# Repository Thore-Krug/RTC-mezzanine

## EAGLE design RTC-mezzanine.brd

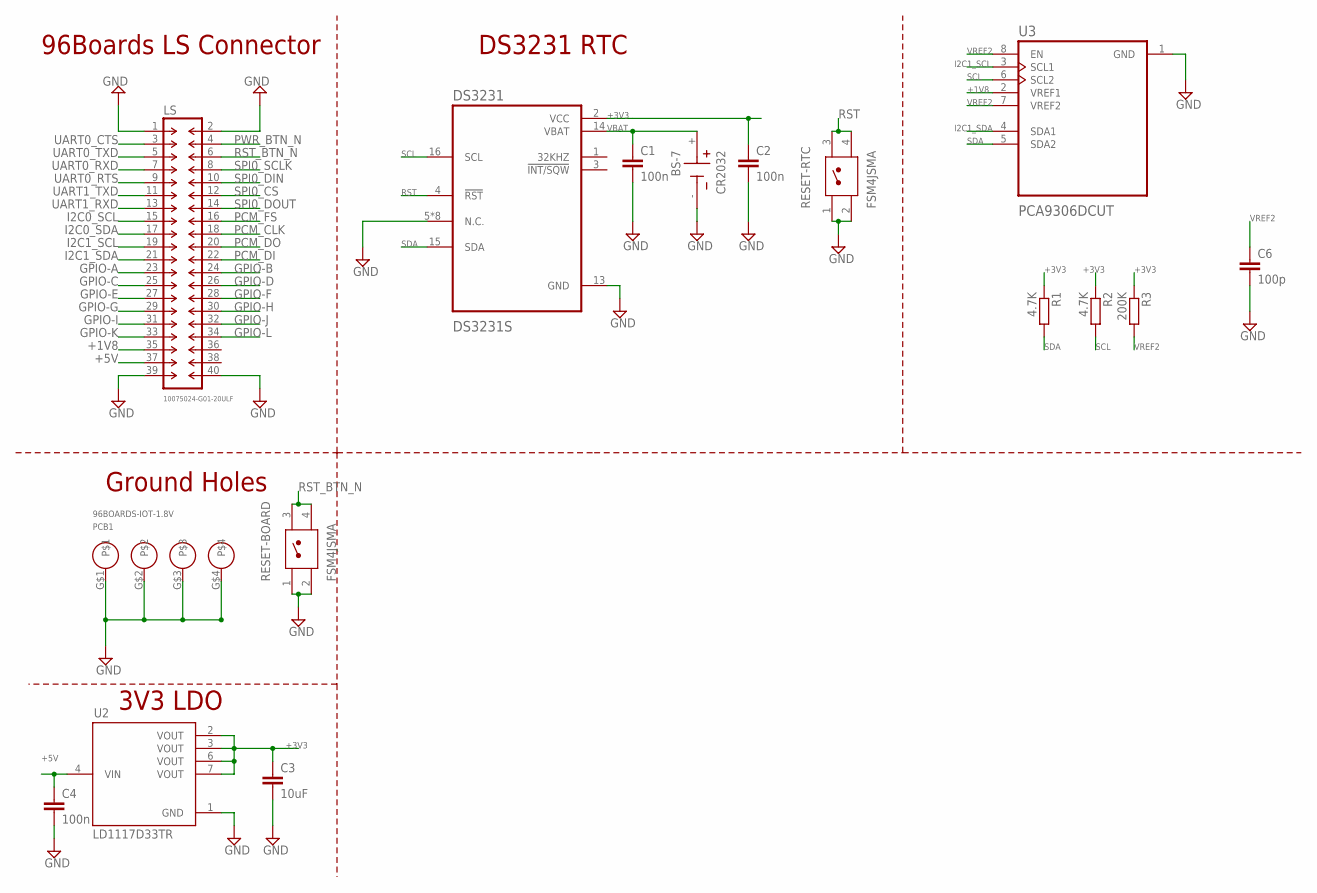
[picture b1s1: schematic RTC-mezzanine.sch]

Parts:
C1, C2, C4: 100n; C0603
C3: 10uF; C0805
C6: 100p; C0603
CR2032: BS-7; BAT_BS-7
DS3231: DS3231S; SOIC127P1032X265-16N
LS: 10075024-G01-20ULF
PCB1: 96BOARDS-IOT-1.8V
R1, R2: 4.7K; R0603
R3: 200K; R0603
RESET-BOARD: FSM4JSMA; TE_FSM4JSMA
RESET-RTC: FSM4JSMA; TE_FSM4JSMA
U2: LD1117D33TR; SOIC127P600X175-8N
U3: PCA9306DCUT; SOP50P310X90-8N

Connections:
+1V8: LS.35, U3.2 (VREF1)
+3V3: C2.1, C3.1, DS3231.2 (VCC), R1.1, R2.1, R3.1, U2.2 (VOUT), U2.3 (VOUT), U2.6 (VOUT), U2.7 (VOUT)
+5V: C4.1, LS.37, U2.4 (VIN)
GND: C1.2, C2.2, C3.2, C4.2, C6.2, CR2032.-, DS3231.5 (N.C.), DS3231.6 (N.C.), DS3231.7 (N.C.), DS3231.8 (N.C.), DS3231.9 (N.C.), DS3231.10 (N.C.), DS3231.11 (N.C.), DS3231.12 (N.C.), DS3231.13 (GND), LS.2, LS.39, LS.40, PCB1.G$1, PCB1.G$2, PCB1.G$3, PCB1.G$4, RESET-BOARD.1, RESET-BOARD.2, RESET-RTC.1, RESET-RTC.2, U2.1 (GND), U3.1 (GND)
GPIO-A: LS.23
GPIO-B: LS.24
GPIO-C: LS.25
GPIO-D: LS.26
GPIO-E: LS.27
GPIO-F: LS.28
GPIO-G: LS.29
GPIO-H: LS.30
GPIO-I: LS.31
GPIO-J: LS.32
GPIO-K: LS.33
GPIO-L: LS.34
I2C0_SCL: LS.15
I2C0_SDA: LS.17
I2C1_SCL: LS.19, U3.3 (SCL1)
I2C1_SDA: LS.21, U3.4 (SDA1)
PCM_CLK: LS.18
PCM_DI: LS.22
PCM_DO: LS.20
PCM_FS: LS.16
PWR_BTN_N: LS.4
RST: DS3231.4 (!RST), RESET-RTC.3, RESET-RTC.4
RST_BTN_N: LS.6, RESET-BOARD.3, RESET-BOARD.4
SCL: DS3231.16 (SCL), R2.2, U3.6 (SCL2)
SDA: DS3231.15 (SDA), R1.2, U3.5 (SDA2)
SPI0_CS: LS.12
SPI0_DIN: LS.10
SPI0_DOUT: LS.14
SPI0_SCLK: LS.8
UART0_CTS: LS.3
UART0_RTS: LS.9
UART0_RXD: LS.7
UART0_TXD: LS.5
UART1_RXD: LS.13
UART1_TXD: LS.11
VBAT: C1.1, CR2032.+, DS3231.14 (VBAT)
VREF2: C6.1, R3.2, U3.7 (VREF2), U3.8 (EN)

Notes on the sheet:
96Boards LS Connector
Ground Holes
DS3231 RTC
3V3 LDO

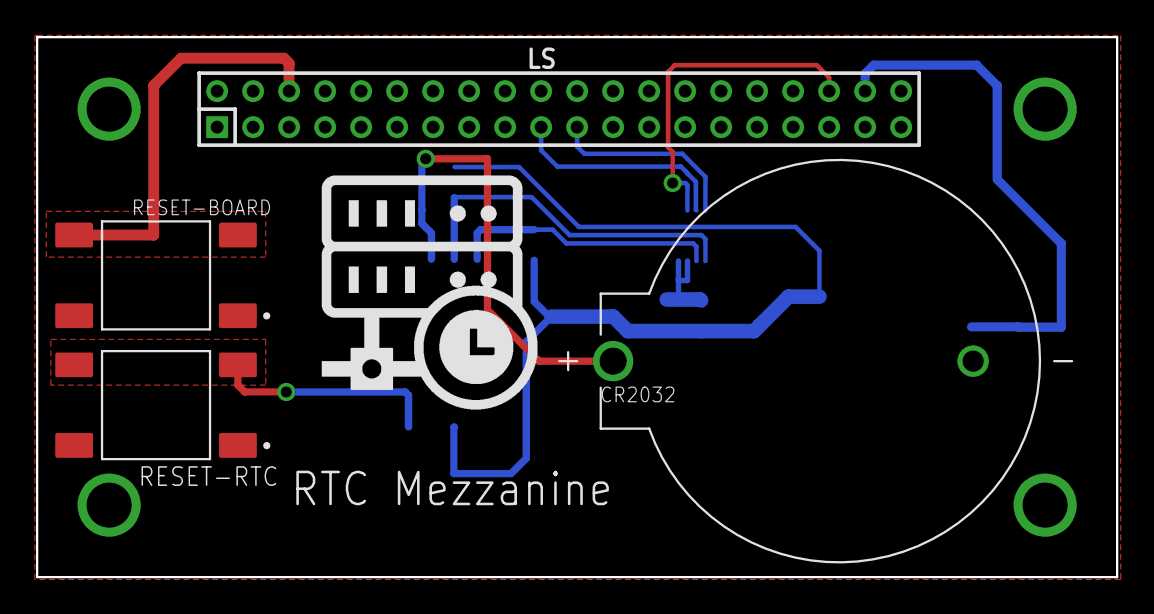
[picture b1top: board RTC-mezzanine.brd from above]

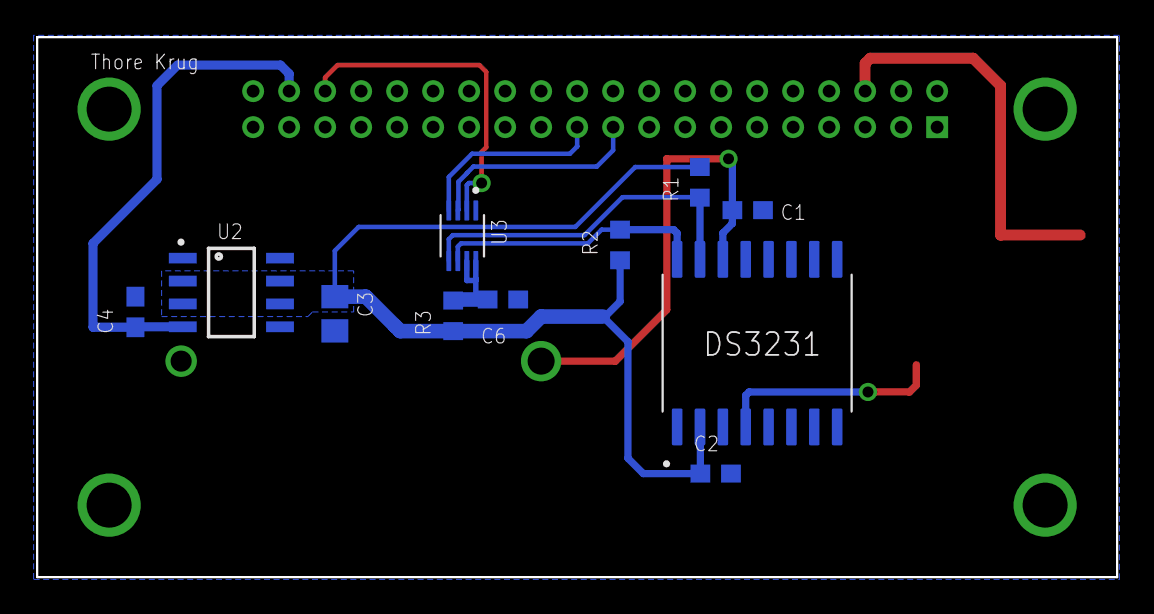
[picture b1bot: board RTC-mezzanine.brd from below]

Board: 2 copper layers, 60.0 x 30.0 mm, 16 parts (11 on the bottom side), 12 nets.

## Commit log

2020-11-16 Adding the Mezzanine Files
    Signed off by: Thore Krug opensource[at]thorekrug.de
